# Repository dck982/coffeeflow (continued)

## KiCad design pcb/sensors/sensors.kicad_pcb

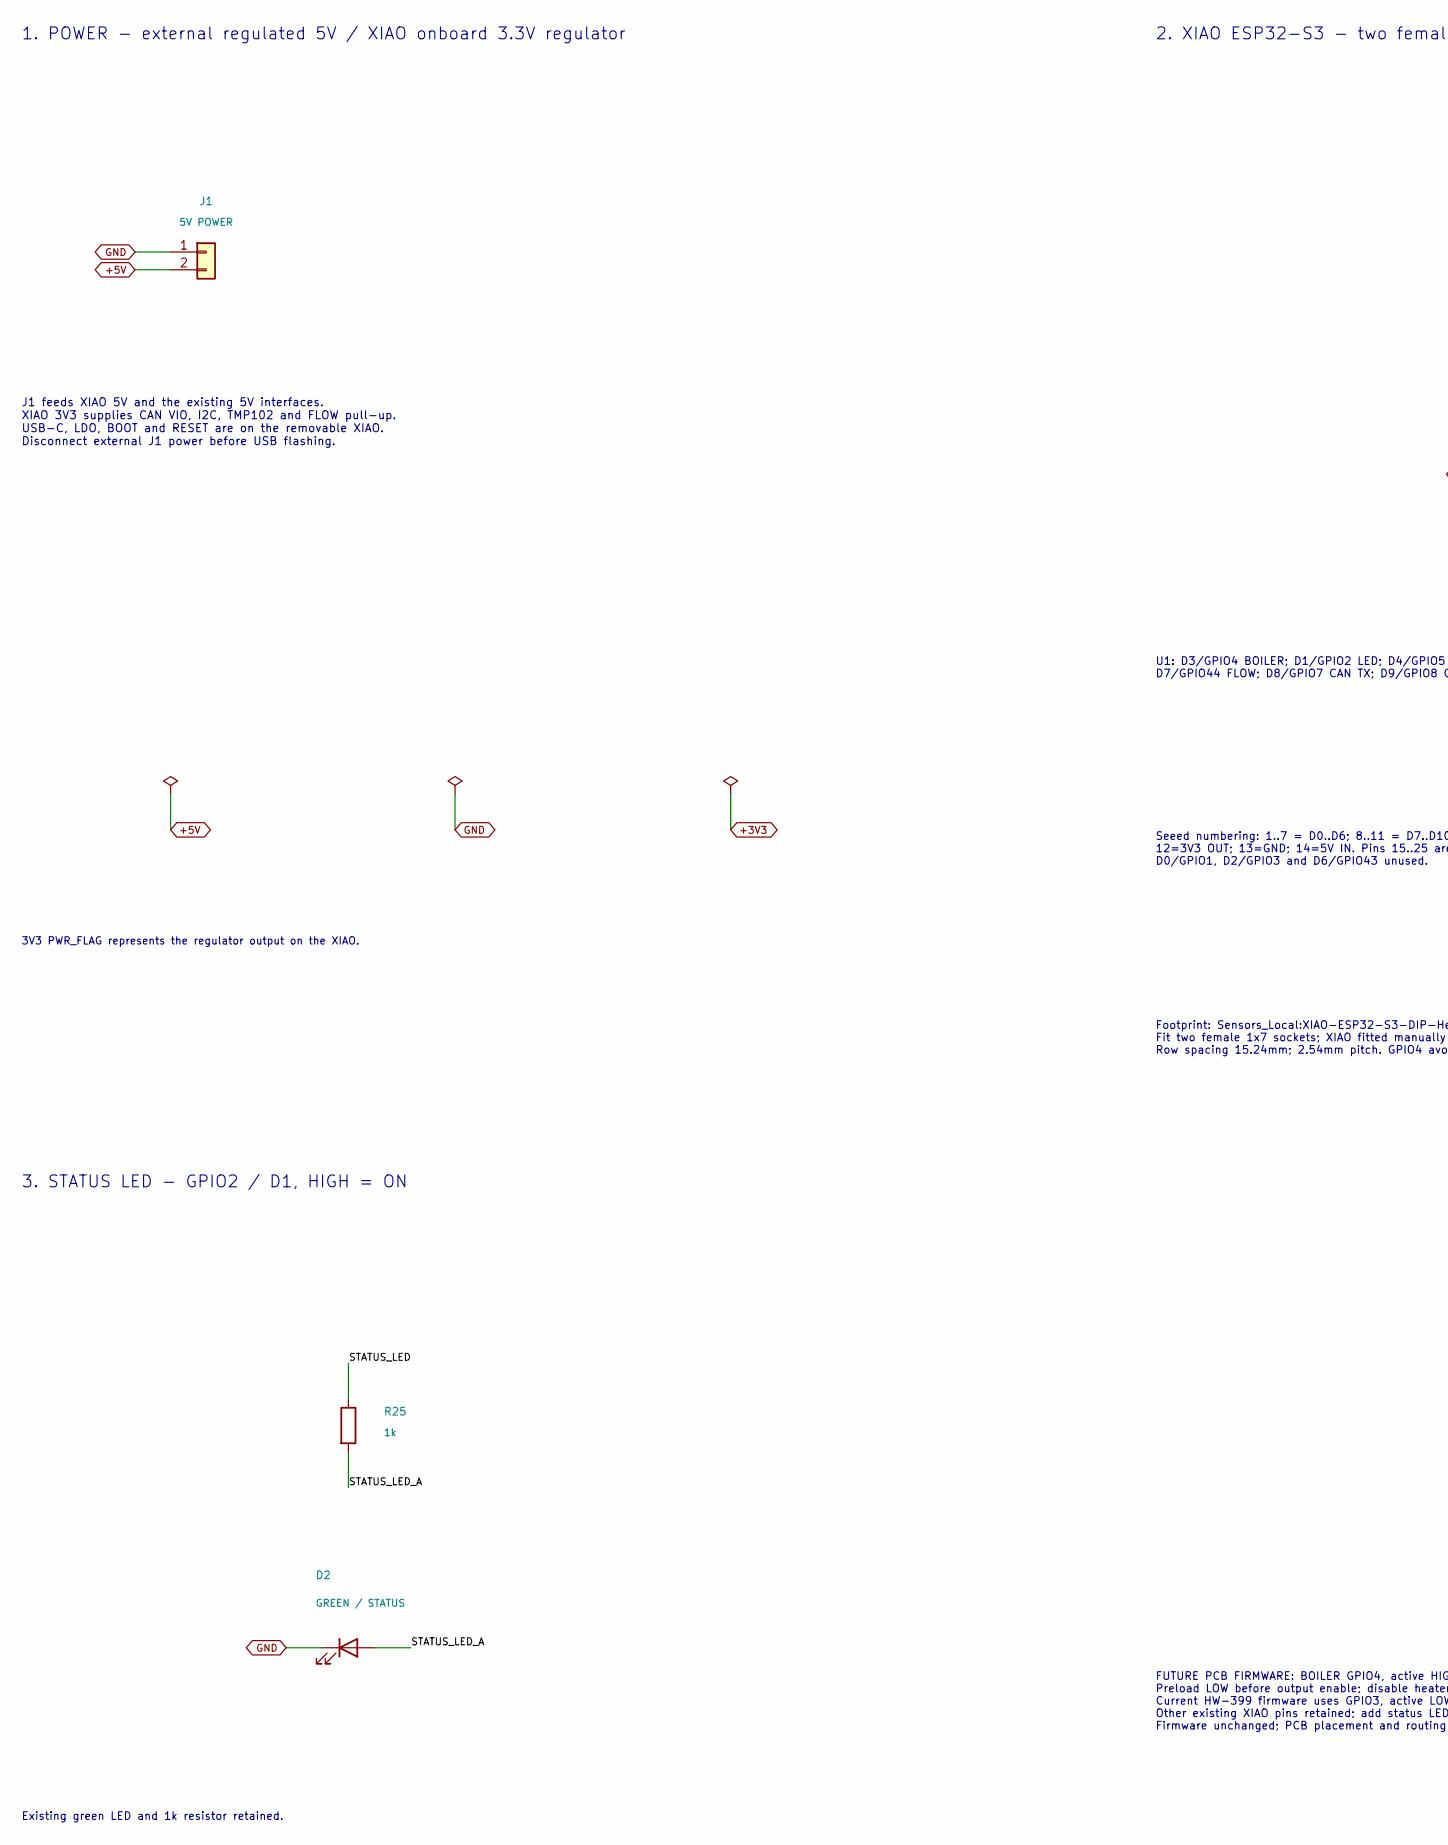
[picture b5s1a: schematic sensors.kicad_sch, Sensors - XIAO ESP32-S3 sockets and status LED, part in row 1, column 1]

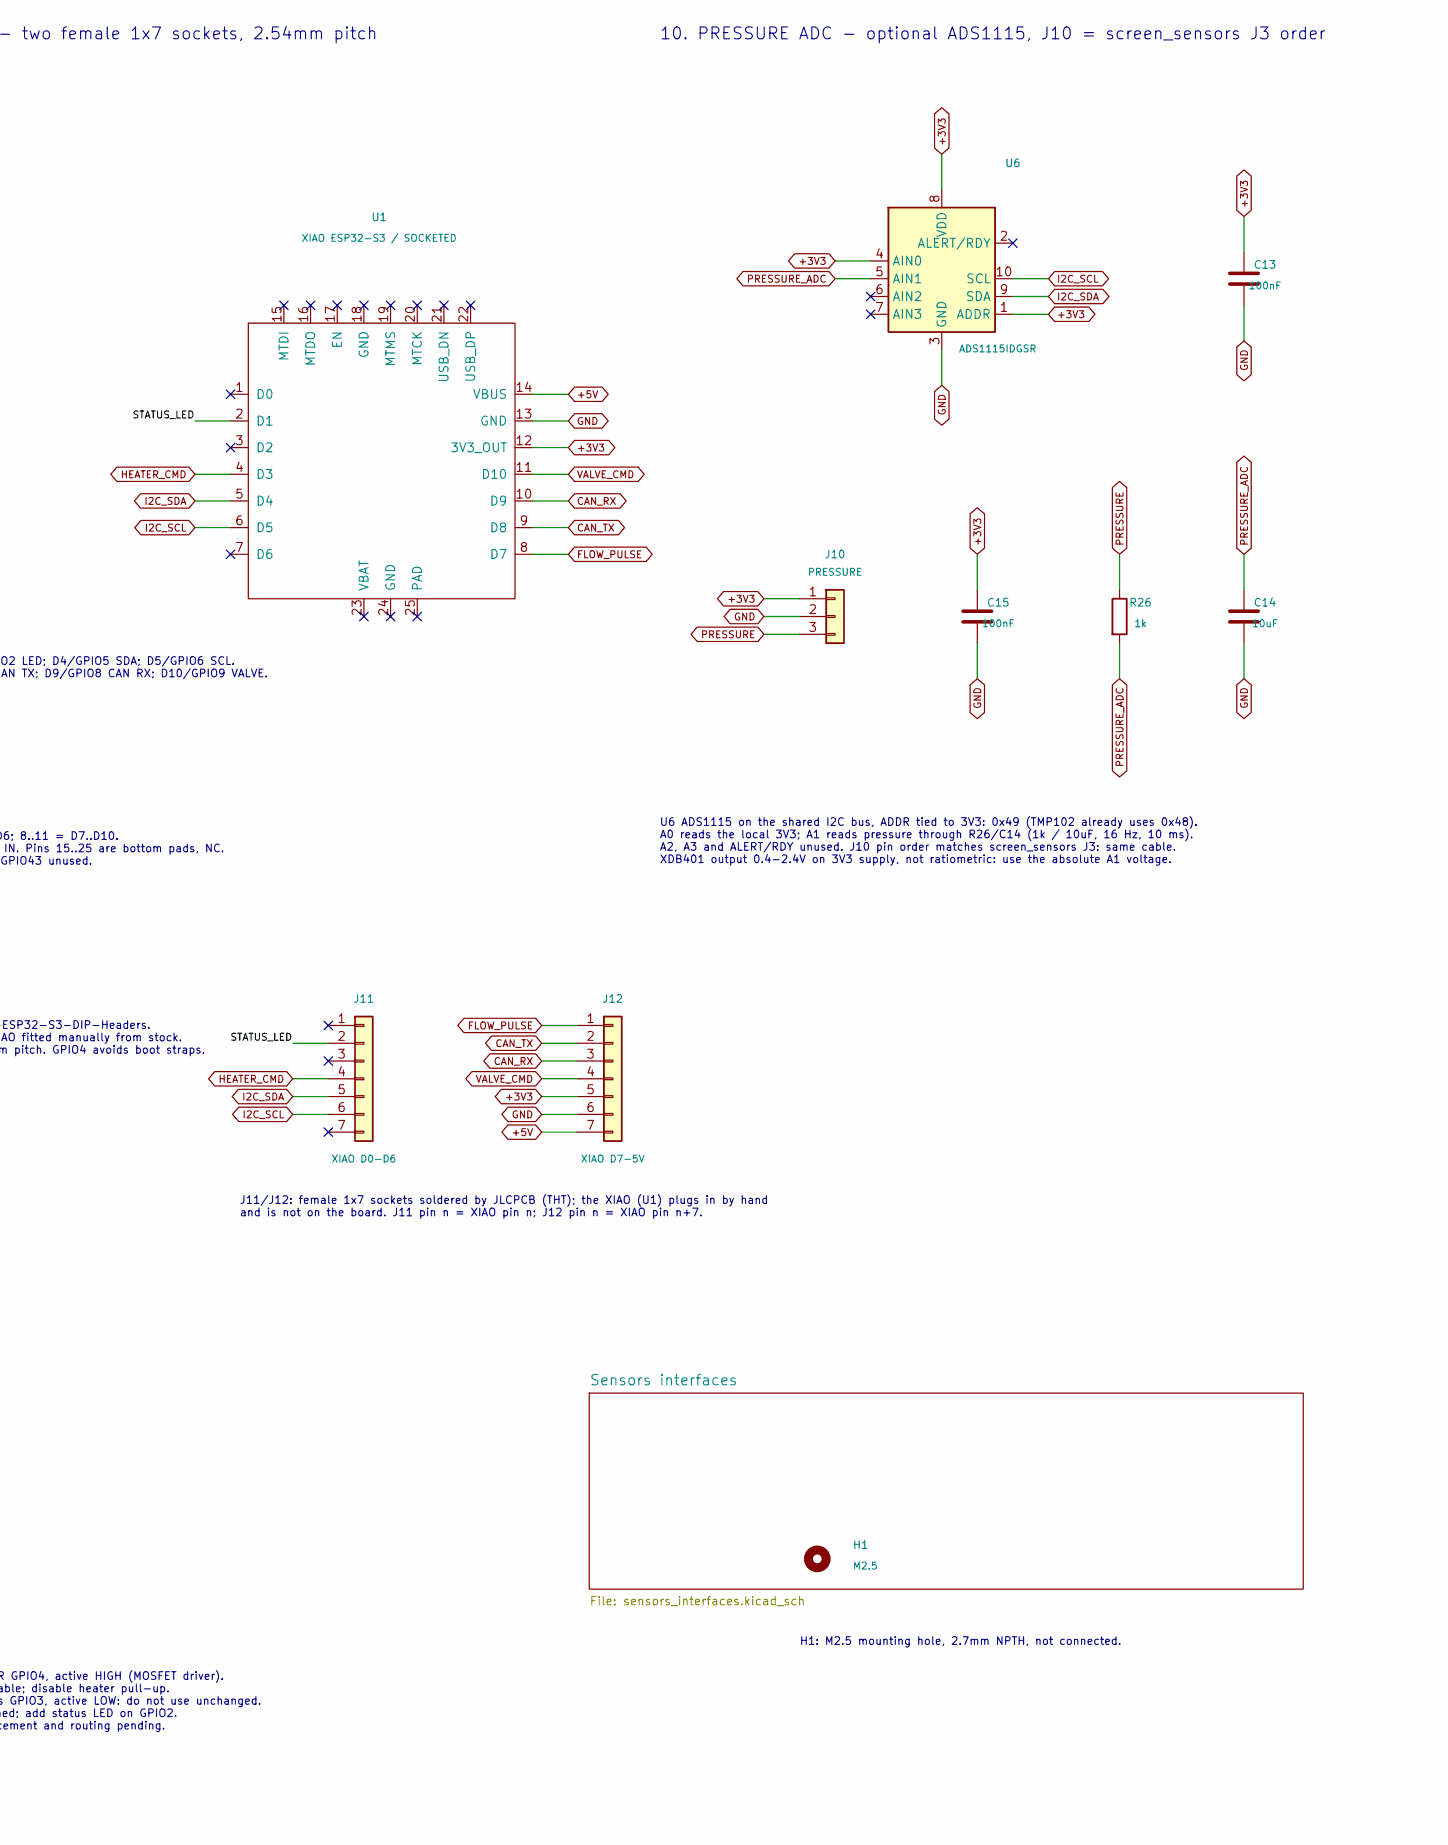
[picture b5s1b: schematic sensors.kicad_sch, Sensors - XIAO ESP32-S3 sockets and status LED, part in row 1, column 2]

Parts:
C13, C15: 100nF; C_0603_1608Metric; MPN CC0603KRX7R9BB104; LCSC C14663
C14: 10uF; C_0603_1608Metric; MPN CL10A106KP8NNNC; LCSC C19702
D2: GREEN / STATUS; LED_0805_2012Metric; MPN KT-0805G; LCSC C2297
H1: M2.5; MountingHole_2.7mm_M2.5; MPN M2.5 / 2.7mm
J1: 5V POWER; JST_XH_B2B-XH-A_1x02_P2.50mm_Vertical; MPN B2B-XH-A(LF)(SN); LCSC C158012
J10: PRESSURE; JST_XH_B3B-XH-A_1x03_P2.50mm_Vertical; MPN B3B-XH-A(LF)(SN); LCSC C144394
J11: XIAO D0-D6; XIAO_Socket_1x07_P2.54mm_Vertical; MPN HX PM2.54-1x7P ZC-Y; LCSC C22438157
J12: XIAO D7-5V; XIAO_Socket_1x07_P2.54mm_Vertical; MPN HX PM2.54-1x7P ZC-Y; LCSC C22438157
R25, R26: 1k; R_0603_1608Metric; MPN 0603WAF1001T5E; LCSC C21190
U1: XIAO ESP32-S3 / SOCKETED; XIAO-ESP32-S3-DIP-Headers; MPN Seeed Studio XIAO ESP32-S3
U6: ADS1115IDGSR; TSSOP-10_3x3mm_P0.5mm; MPN ADS1115IDGSR; LCSC C37593

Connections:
+3V3: C13.1, C15.1, J10.1, J12.5, U1.12 (3V3_OUT), U6.1 (ADDR), U6.4 (AIN0), U6.8 (VDD); also elsewhere on the board
+5V: J1.2, J12.7, U1.14 (VBUS); also elsewhere on the board
/STATUS_LED: J11.2, R25.1, U1.2 (D1)
/STATUS_LED_A: D2.2 (A), R25.2
CAN_RX: J12.3, U1.10 (D9); also elsewhere on the board
CAN_TX: J12.2, U1.9 (D8); also elsewhere on the board
FLOW_PULSE: J12.1, U1.8 (D7); also elsewhere on the board
GND: C13.2, C14.2, C15.2, D2.1 (K), J1.1, J10.2, J12.6, U1.13 (GND), U6.3 (GND); also elsewhere on the board
HEATER_CMD: J11.4, U1.4 (D3); also elsewhere on the board
I2C_SCL: J11.6, U1.6 (D5), U6.10 (SCL); also elsewhere on the board
I2C_SDA: J11.5, U1.5 (D4), U6.9 (SDA); also elsewhere on the board
PRESSURE: J10.3, R26.1
PRESSURE_ADC: C14.1, R26.2, U6.5 (AIN1)
VALVE_CMD: J12.4, U1.11 (D10); also elsewhere on the board

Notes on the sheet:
1. POWER - external regulated 5V / XIAO onboard 3.3V regulator
J1 feeds XIAO 5V and the existing 5V interfaces. XIAO 3V3 supplies CAN VIO, I2C, TMP102 and FLOW pull-up. USB-C, LDO, BOOT and RESET are on the removable XIAO. Disconnect external J1 power before USB flashing.
3V3 PWR_FLAG represents the regulator output on the XIAO.
2. XIAO ESP32-S3 - two female 1x7 sockets, 2.54mm pitch
U1: D3/GPIO4 BOILER; D1/GPIO2 LED; D4/GPIO5 SDA; D5/GPIO6 SCL. D7/GPIO44 FLOW; D8/GPIO7 CAN TX; D9/GPIO8 CAN RX; D10/GPIO9 VALVE.
Seeed numbering: 1..7 = D0..D6; 8..11 = D7..D10. 12=3V3 OUT; 13=GND; 14=5V IN. Pins 15..25 are bottom pads, NC. D0/GPIO1, D2/GPIO3 and D6/GPIO43 unused.
Footprint: Sensors_Local:XIAO-ESP32-S3-DIP-Headers. Fit two female 1x7 sockets; XIAO fitted manually from stock. Row spacing 15.24mm; 2.54mm pitch. GPIO4 avoids boot straps.
3. STATUS LED - GPIO2 / D1, HIGH = ON
Existing green LED and 1k resistor retained.
FUTURE PCB FIRMWARE: BOILER GPIO4, active HIGH (MOSFET driver). Preload LOW before output enable; disable heater pull-up. Current HW-399 firmware uses GPIO3, active LOW: do not use unchanged. Other existing XIAO pins retained; add status LED on GPIO2. Firmware unchanged; PCB placement and routing p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
J11/J12: female 1x7 sockets soldered by JLCPCB (THT); the XIAO (U1) plugs in by hand and is not on the board. J11 pin n = XIAO pin n; J12 pin n = XIAO pin n+7.
H1: M2.5 mounting hole, 2.7mm NPTH, not connected.
10. PRESSURE ADC - optional ADS1115, J10 = screen_sensors J3 order
U6 ADS1115 on the shared I2C bus, ADDR tied to 3V3: 0x49 (TMP102 already uses 0x48). A0 reads the local 3V3; A1 reads pressure through R26/C14 (1k / 10uF, 16 Hz, 10 ms). A2, A3 and ALERT/RDY unused. J10 pin order matches screen_sensors J3: same cable. XDB401 output 0.4-2.4V on 3V3 supply, not ratio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

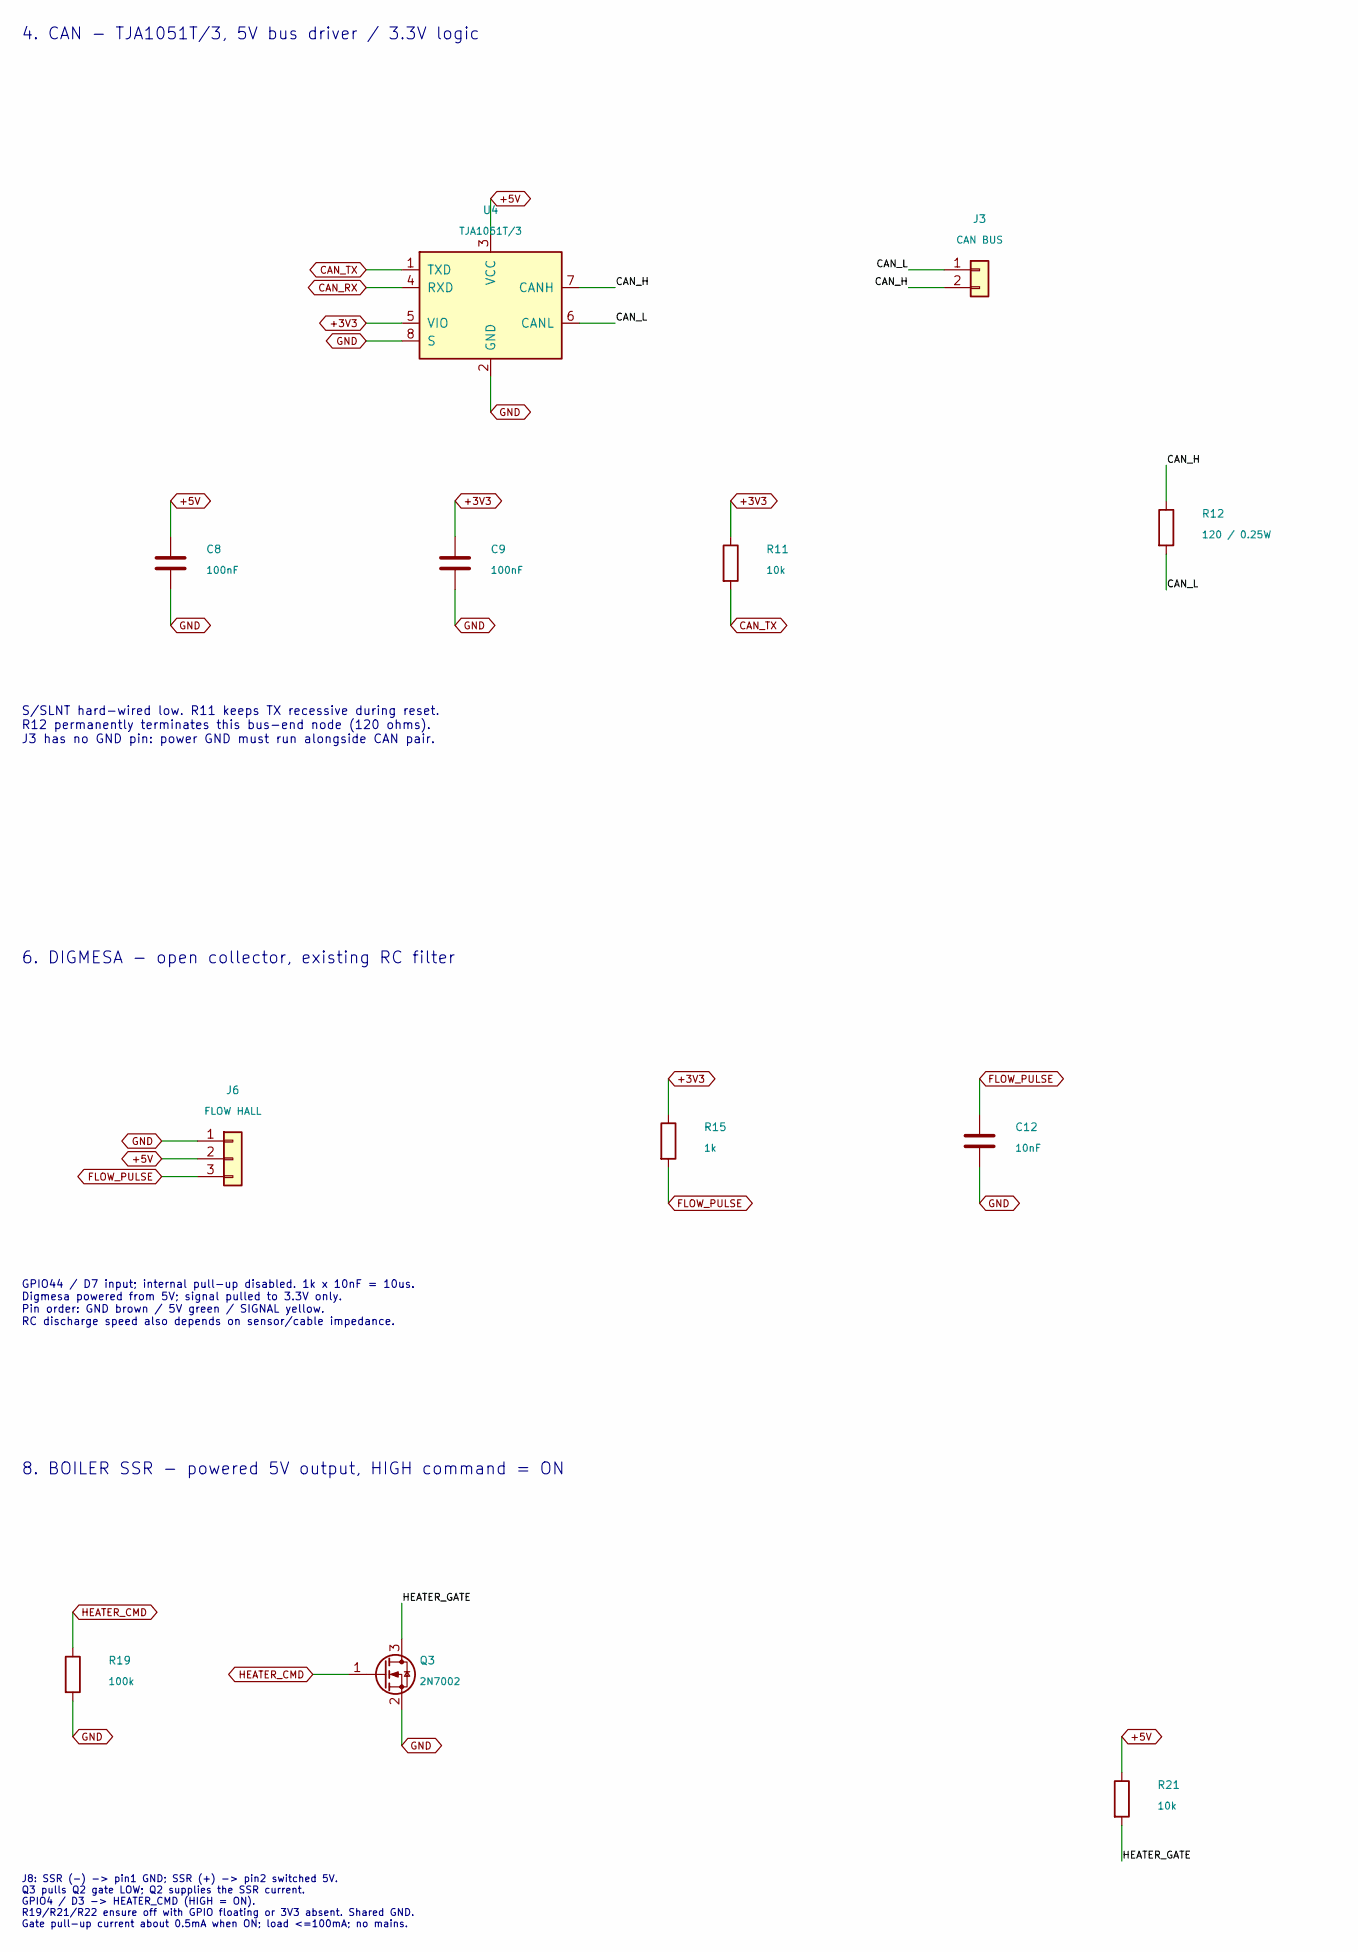
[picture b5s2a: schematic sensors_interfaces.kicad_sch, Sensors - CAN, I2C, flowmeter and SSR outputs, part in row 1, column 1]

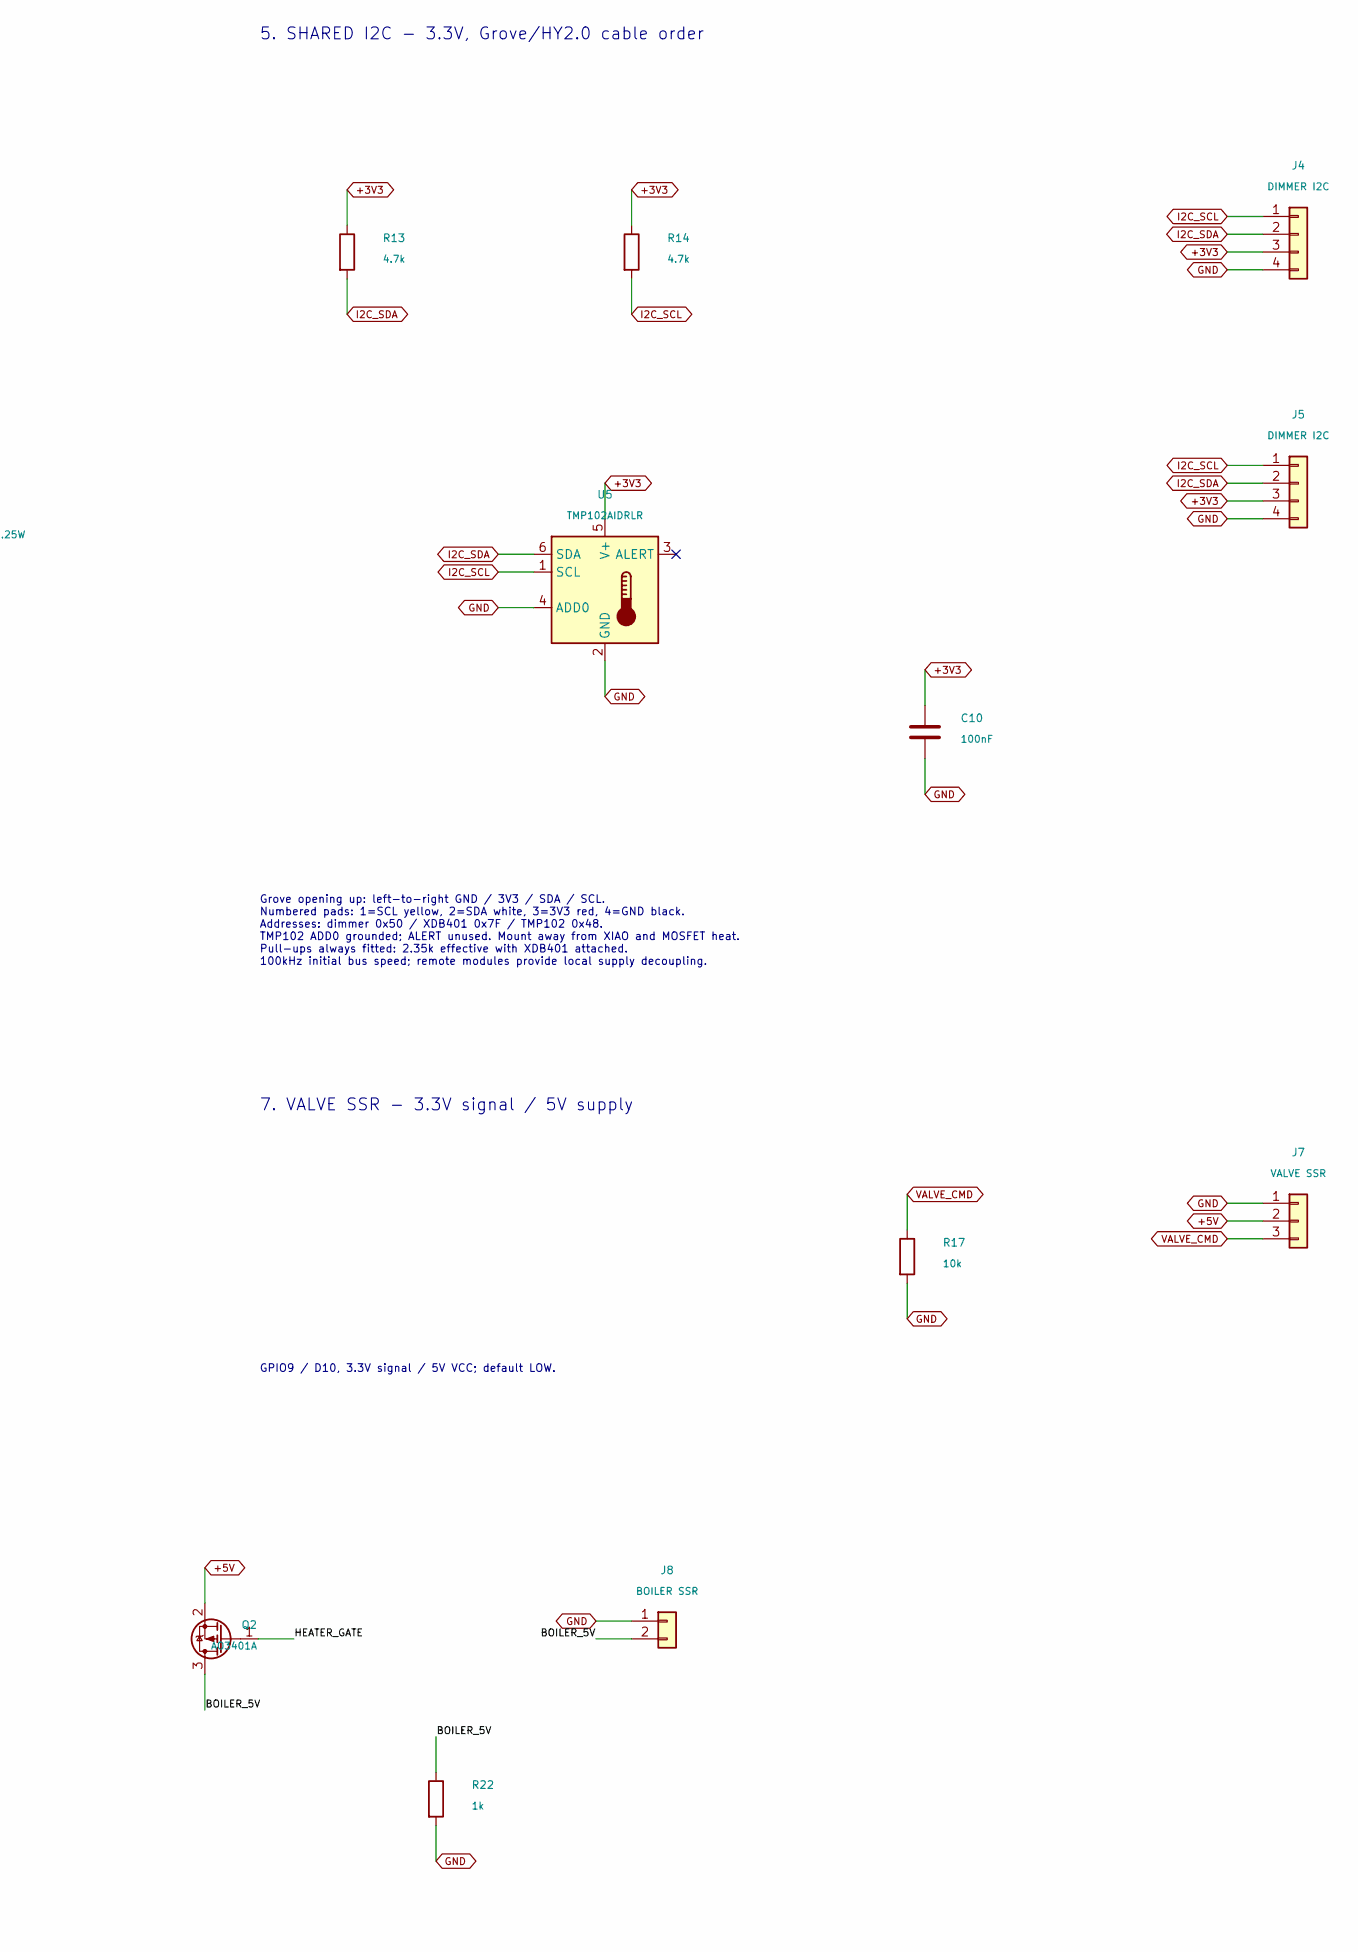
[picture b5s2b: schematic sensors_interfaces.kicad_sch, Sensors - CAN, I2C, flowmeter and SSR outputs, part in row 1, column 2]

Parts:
C8, C9, C10: 100nF; C_0603_1608Metric; MPN CC0603KRX7R9BB104; LCSC C14663
C12: 10nF; C_0603_1608Metric; MPN 0603B103K500NT; LCSC C57112
J3: CAN BUS; JST_XH_B2B-XH-A_1x02_P2.50mm_Vertical; MPN B2B-XH-A(LF)(SN); LCSC C158012
J4, J5: DIMMER I2C; CONN-TH_HY-4A; MPN HY-4A; LCSC C722737
J6: FLOW HALL; JST_XH_B3B-XH-A_1x03_P2.50mm_Vertical; MPN B3B-XH-A(LF)(SN); LCSC C144394
J7: VALVE SSR; JST_XH_B3B-XH-A_1x03_P2.50mm_Vertical; MPN B3B-XH-A(LF)(SN); LCSC C144394
J8: BOILER SSR; JST_XH_B2B-XH-A_1x02_P2.50mm_Vertical; MPN B2B-XH-A(LF)(SN); LCSC C158012
Q2: AO3401A; SOT-23; MPN AO3401A; LCSC C15127
Q3: 2N7002; SOT-23; MPN 2N7002; LCSC C8545
R11, R17, R21: 10k; R_0603_1608Metric; MPN 0603WAF1002T5E; LCSC C25804
R12: 120 / 0.25W; R_1206_3216Metric; MPN 1206W4F1200T5E; LCSC C17909
R13, R14: 4.7k; R_0603_1608Metric; MPN 0603WAF4701T5E; LCSC C23162
R15, R22: 1k; R_0603_1608Metric; MPN 0603WAF1001T5E; LCSC C21190
R19: 100k; R_0603_1608Metric; MPN 0603WAF1003T5E; LCSC C25803
U4: TJA1051T/3; SOIC-8_3.9x4.9mm_P1.27mm; MPN TJA1051T/3/1J; LCSC C38695
U5: TMP102AIDRLR; SOT-563; MPN TMP102AIDRLR; LCSC C99269

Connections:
+3V3: C9.1, C10.1, J4.3, J5.3, R11.1, R13.1, R14.1, R15.1, U4.5 (VIO), U5.5 (V+); also elsewhere on the board
+5V: C8.1, J6.2, J7.2, Q2.2 (S), R21.1, U4.3 (VCC); also elsewhere on the board
/Sensors interfaces/BOILER_5V: J8.2, Q2.3 (D), R22.1
/Sensors interfaces/CAN_H: J3.2, R12.1, U4.7 (CANH)
/Sensors interfaces/CAN_L: J3.1, R12.2, U4.6 (CANL)
/Sensors interfaces/HEATER_GATE: Q2.1 (G), Q3.3 (D), R21.2
CAN_RX: U4.4 (RXD); also elsewhere on the board
CAN_TX: R11.2, U4.1 (TXD); also elsewhere on the board
FLOW_PULSE: C12.1, J6.3, R15.2; also elsewhere on the board
GND: C8.2, C9.2, C10.2, C12.2, J4.4, J5.4, J6.1, J7.1, J8.1, Q3.2 (S), R17.2, R19.2, R22.2, U4.2 (GND), U4.8 (S), U5.2 (GND), U5.4 (ADD0); also elsewhere on the board
HEATER_CMD: Q3.1 (G), R19.1; also elsewhere on the board
I2C_SCL: J4.1, J5.1, R14.2, U5.1 (SCL); also elsewhere on the board
I2C_SDA: J4.2, J5.2, R13.2, U5.6 (SDA); also elsewhere on the board
VALVE_CMD: J7.3, R17.1; also elsewhere on the board

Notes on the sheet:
8. BOILER SSR - powered 5V output, HIGH command = ON
5. SHARED I2C - 3.3V, Grove/HY2.0 cable order
4. CAN - TJA1051T/3, 5V bus driver / 3.3V logic
6. DIGMESA - open collector, existing RC filter
Grove opening up: left-to-right GND / 3V3 / SDA / SCL. Numbered pads: 1=SCL yellow, 2=SDA white, 3=3V3 red, 4=GND black. Addresses: dimmer 0x50 / XDB401 0x7F / TMP102 0x48. TMP102 ADD0 grounded; ALERT unused. Mount away from XIAO and MOSFET heat. Pull-ups always fitted: 2.35k effective with XDB401 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
GPIO9 / D10, 3.3V signal / 5V VCC; default LOW.
S/SLNT hard-wired low. R11 keeps TX recessive during reset. R12 permanently terminates this bus-end node (120 ohms). J3 has no GND pin: power GND must run alongside CAN pair.
7. VALVE SSR - 3.3V signal / 5V supply
J8: SSR (-) -> pin1 GND; SSR (+) -> pin2 switched 5V. Q3 pulls Q2 gate LOW; Q2 supplies the SSR current. GPIO4 / D3 -> HEATER_CMD (HIGH = ON). R19/R21/R22 ensure off with GPIO floating or 3V3 absent. Shared GND. Gate pull-up current about 0.5mA when ON; load <=100mA; no mains.
GPIO44 / D7 input; internal pull-up disabled. 1k x 10nF = 10us. Digmesa powered from 5V; signal pulled to 3.3V only. Pin order: GND brown / 5V green / SIGNAL yellow. RC discharge speed also depends on sensor/cable impedance.

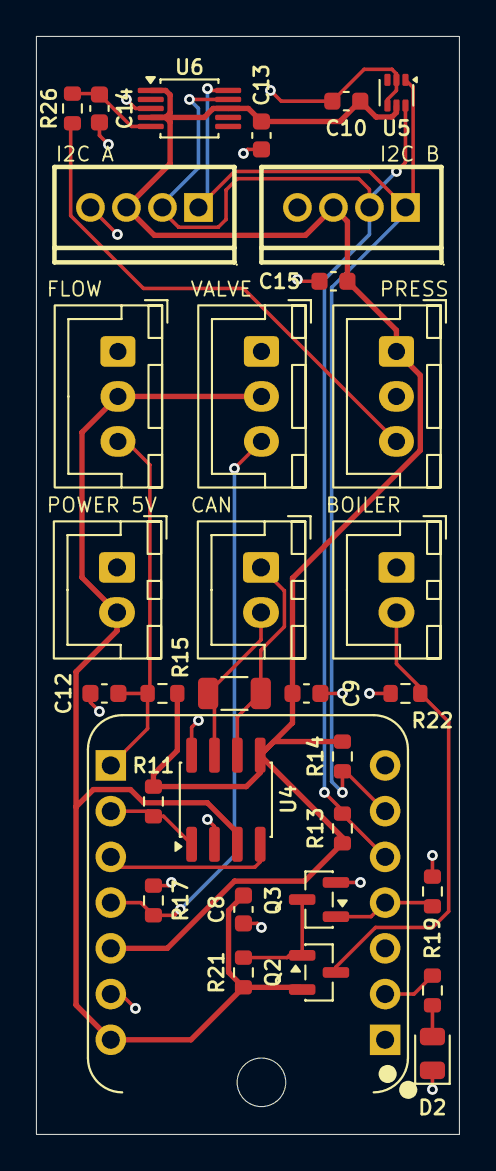
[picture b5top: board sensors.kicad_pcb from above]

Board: 2 copper layers, 23.5 x 61.0 mm, 35 parts (0 on the bottom side), 18 nets.

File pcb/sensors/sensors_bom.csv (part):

Reference,Value,Footprint,DNP,LCSC,MPN,Description,Sheet,SchematicReference,Manufacturer,JLCClass,Assembly,CheckedDate,SourceURL,Notes
C8,100nF,Capacitor_SMD:C_0603_1608Metric,False,C14663,CC0603KRX7R9BB104,Unpolarized capacitor,sensors_interfaces.kicad_sch,C8,YAGEO,Basic,SMT,2026-10-11,https://jlcpcb.com/partdetail/x/C14663,
C9,100nF,Capacitor_SMD:C_0603_1608Metric,False,C14663,CC0603KRX7R9BB104,Unpolarized capacitor,sensors_interfaces.kicad_sch,C9,YAGEO,Basic,SMT,2026-10-11,https://jlcpcb.com/partdetail/x/C14663,
C10,100nF,Capacitor_SMD:C_0603_1608Metric,False,C14663,CC0603KRX7R9BB104,Unpolarized capacitor,sensors_interfaces.kicad_sch,C10,YAGEO,Basic,SMT,2026-10-11,https://jlcpcb.com/partdetail/x/C14663,
C12,10nF,Capacitor_SMD:C_0603_1608Metric,False,C57112,0603B103K500NT,Unpolarized capacitor,sensors_interfaces.kicad_sch,C12,FH (Guangdong Fenghua Advanced Tech),Basic,SMT,2026-10-11,https://jlcpcb.com/partdetail/x/C57112,
C13,100nF,Capacitor_SMD:C_0603_1608Metric,False,C14663,CC0603KRX7R9BB104,At U6 VDD,sensors.kicad_sch,C13,YAGEO,Basic,SMT,2026-10-11,https://jlcpcb.com/partdetail/x/C14663,100nF 50V X7R 0603; U6 ADS1115 decoupling.
C14,10uF,Capacitor_SMD:C_0603_1608Metric,False,C19702,CL10A106KP8NNNC,1k/10uF fc~16Hz; X5R 10V,sensors.kicad_sch,C14,Samsung Electro-Mechanics,Basic,SMT,2026-10-11,https://jlcpcb.com/partdetail/x/C19702,10uF 10V X5R 0603; pressure input filter with R26 (16 Hz).
C15,100nF,Capacitor_SMD:C_0603_1608Metric,False,C14663,CC0603KRX7R9BB104,At J10 supply,sensors.kicad_sch,C15,YAGEO,Basic,SMT,2026-10-11,https://jlcpcb.com/partdetail/x/C14663,100nF 50V X7R 0603; decoupling at the J10 pressure sensor supply.
D2,GREEN / STATUS,LED_SMD:LED_0805_2012Metric,False,C2297,KT-0805G,"Green status LED, pin 1 cathode to GND",sensors.kicad_sch,D2,Hubei KENTO Elec,Basic,SMT,2026-10-11,https://jlcpcb.com/partdetail/x/C2297,"Emerald green 0805; pin 1 cathode to GND, pin 2 anode via R25 (1k) from GPIO2."
J1,5V POWER,Connector_JST:JST_XH_B2B-XH-A_1x02_P2.50mm_Vertical,False,C158012,B2B-XH-A(LF)(SN),"Generic connector, single row, 01x02, script generated (kicad-library-utils/schlib/autogen/connector/)",sensors.kicad_sch,J1,JST,Extended,THT,2026-10-11,https://jlcpcb.com/partdetail/x/C158012,
J3,CAN BUS,Connector_JST:JST_XH_B2B-XH-A_1x02_P2.50mm_Vertical,False,C158012,B2B-XH-A(LF)(SN),"Generic connector, single row, 01x02, script generated (kicad-library-utils/schlib/autogen/connector/)",sensors_interfaces.kicad_sch,J3,JST,Extended,THT,2026-10-11,https://jlcpcb.com/partdetail/x/C158012,
J4,DIMMER I2C,Sensors_Local:CONN-TH_HY-4A,False,C722737,HY-4A,"Generic connector, single row, 01x04, script generated (kicad-library-utils/schlib/autogen/connector/)",sensors_interfaces.kicad_sch,J4,CAX,Extended,THT,2026-10-11,https://jlcpcb.com/partdetail/x/C722737,"CAX vertical HY 4-pin, 2mm pitch; user confirmed model displays in JLCPCB. Retain NS-Tech Grove pin layout, but update PCB drills to supplier CAD 1.0mm (current drills 0.762mm). CPL uses pin-row midpoint and -90 degree rotation offset matched to supplier pad numbering."
J5,DIMMER I2C,Sensors_Local:CONN-TH_HY-4A,False,C722737,HY-4A,"Generic connector, single row, 01x04, script generated (kicad-library-utils/schlib/autogen/connector/)",sensors_interfaces.kicad_sch,J5,CAX,Extended,THT,2026-10-11,https://jlcpcb.com/partdetail/x/C722737,"Second parallel Grove I2C connector (PCB I2C A), same SCL/SDA/3V3/GND bus and C722737 sourcing as J4 (I2C B)."
J6,FLOW HALL,Connector_JST:JST_XH_B3B-XH-A_1x03_P2.50mm_Vertical,False,C144394,B3B-XH-A(LF)(SN),"Generic connector, single row, 01x03, script generated (kicad-library-utils/schlib/autogen/connector/)",sensors_interfaces.kicad_sch,J6,JST,Extended,THT,2026-10-11,https://jlcpcb.com/partdetail/x/C144394,
J7,VALVE SSR,Connector_JST:JST_XH_B3B-XH-A_1x03_P2.50mm_Vertical,False,C144394,B3B-XH-A(LF)(SN),"Generic connector, single row, 01x03, script generated (kicad-library-utils/schlib/autogen/connector/)",sensors_interfaces.kicad_sch,J7,JST,Extended,THT,2026-10-11,https://jlcpcb.com/partdetail/x/C144394,
J8,BOILER SSR,Connector_JST:JST_XH_B2B-XH-A_1x02_P2.50mm_Vertical,False,C158012,B2B-XH-A(LF)(SN),"Generic connector, single row, 01x02, script generated (kicad-library-utils/schlib/autogen/connector/)",sensors_interfaces.kicad_sch,J8,JST,Extended,THT,2026-10-11,https://jlcpcb.com/partdetail/x/C158012,
J10,PRESSURE,Connector_JST:JST_XH_B3B-XH-A_1x03_P2.50mm_Vertical,False,C144394,B3B-XH-A(LF)(SN),"Pin 1 3V3, 2 GND, 3 sensor output",sensors.kicad_sch,J10,JST,Extended,THT,2026-10-11,https://jlcpcb.com/partdetail/x/C144394,"Pressure sensor input: pin 1 3V3, 2 GND, 3 output."
J11,XIAO D0-D6,Sensors_Local:XIAO_Socket_1x07_P2.54mm_Vertical,False,C22438157,HX PM2.54-1x7P ZC-Y,Female 1x7 socket for XIAO pins 1-7 (D0-D6),sensors.kicad_sch,J11,hanxia,Extended,THT,2026-10-11,https://jlcpcb.com/partdetail/x/C22438157,"Female 1x7 2.54 mm socket, 8.5 mm high, for XIAO pins 1-7. Soldered by JLCPCB (THT); the XIAO plugs in by hand."
J12,XIAO D7-5V,Sensors_Local:XIAO_Socket_1x07_P2.54mm_Vertical,False,C22438157,HX PM2.54-1x7P ZC-Y,"Female 1x7 socket for XIAO pins 8-14 (D7-D10, 3V3, GND, 5V)",sensors.kicad_sch,J12,hanxia,Extended,THT,2026-10-11,https://jlcpcb.com/partdetail/x/C22438157,"Female 1x7 2.54 mm socket, 8.5 mm high, for XIAO pins 8-14. Soldered by JLCPCB (THT); the XIAO plugs in by hand."
Q2,AO3401A,Package_TO_SOT_SMD:SOT-23,False,C15127,AO3401A,"-4.0A Id, -30V Vds, P-Channel MOSFET, SOT-23",sensors_interfaces.kicad_sch,Q2,Alpha & Omega Semicon,Basic,SMT,2026-10-11,https://jlcpcb.com/partdetail/x/C15127,
Q3,2N7002,Package_TO_SOT_SMD:SOT-23,False,C8545,2N7002,"0.115A Id, 60V Vds, N-Channel MOSFET, SOT-23",sensors_interfaces.kicad_sch,Q3,"Jiangsu Changjing Electronics Technology Co., Ltd.",Basic,SMT,2026-10-11,https://jlcpcb.com/partdetail/x/C8545,
R11,10k,Resistor_SMD:R_0603_1608Metric,False,C25804,0603WAF1002T5E,Resistor,sensors_interfaces.kicad_sch,R11,UNI-ROYAL(Uniroyal Elec),Basic,SMT,2026-10-11,https://jlcpcb.com/partdetail/x/C25804,
R12,120 / 0.25W,Resistor_SMD:R_1206_3216Metric,False,C17909,1206W4F1200T5E,Resistor,sensors_interfaces.kicad_sch,R12,UNI-ROYAL(Uniroyal Elec),Basic,SMT,2026-10-11,https://jlcpcb.com/partdetail/x/C17909,
R13,4.7k,Resistor_SMD:R_0603_1608Metric,False,C23162,0603WAF4701T5E,Resistor,sensors_interfaces.kicad_sch,R13,UNI-ROYAL(Uniroyal Elec),Basic,SMT,2026-10-11,https://jlcpcb.com/partdetail/x/C23162,
R14,4.7k,Resistor_SMD:R_0603_1608Metric,False,C23162,0603WAF4701T5E,Resistor,sensors_interfaces.kicad_sch,R14,UNI-ROYAL(Uniroyal Elec),Basic,SMT,2026-10-11,https://jlcpcb.com/partdetail/x/C23162,
R15,1k,Resistor_SMD:R_0603_1608Metric,False,C21190,0603WAF1001T5E,Resistor,sensors_interfaces.kicad_sch,R15,UNI-ROYAL(Uniroyal Elec),Basic,SMT,2026-10-11,https://jlcpcb.com/partdetail/x/C21190,
R17,10k,Resistor_SMD:R_0603_1608Metric,False,C25804,0603WAF1002T5E,Resistor,sensors_interfaces.kicad_sch,R17,UNI-ROYAL(Uniroyal Elec),Basic,SMT,2026-10-11,https://jlcpcb.com/partdetail/x/C25804,
R19,100k,Resistor_SMD:R_0603_1608Metric,False,C25803,0603WAF1003T5E,Resistor,sensors_interfaces.kicad_sch,R19,UNI-ROYAL(Uniroyal Elec),Basic,SMT,2026-10-11,https://jlcpcb.com/partdetail/x/C25803,
R21,10k,Resistor_SMD:R_0603_1608Metric,False,C25804,0603WAF1002T5E,Resistor,sensors_interfaces.kicad_sch,R21,UNI-ROYAL(Uniroyal Elec),Basic,SMT,2026-10-11,https://jlcpcb.com/partdetail/x/C25804,
R22,1k,Resistor_SMD:R_0603_1608Metric,False,C21190,0603WAF1001T5E,Resistor,sensors_interfaces.kicad_sch,R22,UNI-ROYAL(Uniroyal Elec),Basic,SMT,2026-10-11,https://jlcpcb.com/partdetail/x/C21190,
R25,1k,Resistor_SMD:R_0603_1608Metric,False,C21190,0603WAF1001T5E,Resistor,sensors.kicad_sch,R25,UNI-ROYAL(Uniroyal Elec),Basic,SMT,2026-10-11,https://jlcpcb.com/partdetail/x/C21190,
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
